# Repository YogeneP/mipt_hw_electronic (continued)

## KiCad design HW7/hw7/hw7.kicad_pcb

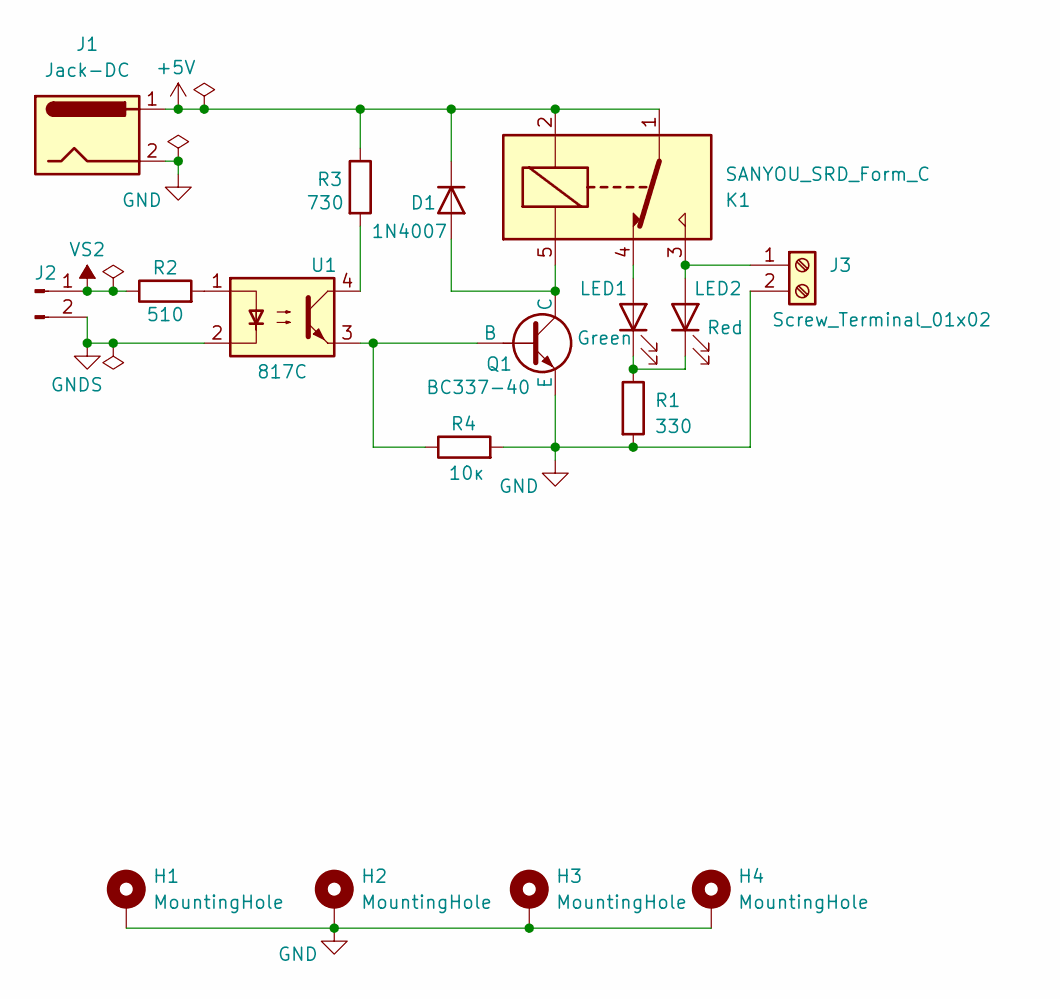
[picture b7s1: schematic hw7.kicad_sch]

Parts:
D1: 1N4007; D_0805_2012Metric
H1, H2, H3, H4: MountingHole; MountingHole_2.2mm_M2_DIN965_Pad
J1: Jack-DC; BarrelJack_GCT_DCJ200-10-A_Horizontal
J2: Conn_01x02_Pin; Molex_KK-254_AE-6410-02A_1x02_P2.54mm_Vertical
J3: Screw_Terminal_01x02; TerminalBlock_Phoenix_MKDS-1,5-2-5.08_1x02_P5.08mm_Horizont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
K1: SANYOU_SRD_Form_C; Relay_SPDT_SANYOU_SRD_Series_Form_C
LED1: Red; LED_1210_3225Metric
LED2: Green; LED_1210_3225Metric
Q1: BC337-40; TO-92L
R1: 330; R_0805_2012Metric_Pad1.20x1.40mm_HandSolder
R2: 510; R_0805_2012Metric_Pad1.20x1.40mm_HandSolder
R3: 730; R_0805_2012Metric_Pad1.20x1.40mm_HandSolder
R4: 10к; R_0805_2012Metric_Pad1.20x1.40mm_HandSolder
U1: 817C; DIP-4_W7.62mm_LongPads

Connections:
+5V: D1.1 (K), J1.1, K1.1, K1.2, R3.1
GND: H1.1, H2.1, H3.1, H4.1, J1.2, J3.2, Q1.3 (E), R1.2, R4.2
GNDS: J2.2, U1.2
unnamed: D1.2 (A), K1.5, Q1.1 (C)
unnamed: J3.1, K1.3, LED2.2 (A)
unnamed: K1.4, LED1.2 (A)
unnamed: LED1.1 (K), LED2.1 (K), R1.1
unnamed: Q1.2 (B), R4.1, U1.3
unnamed: R2.2, U1.1
unnamed: R3.2, U1.4
VS2: J2.1, R2.1

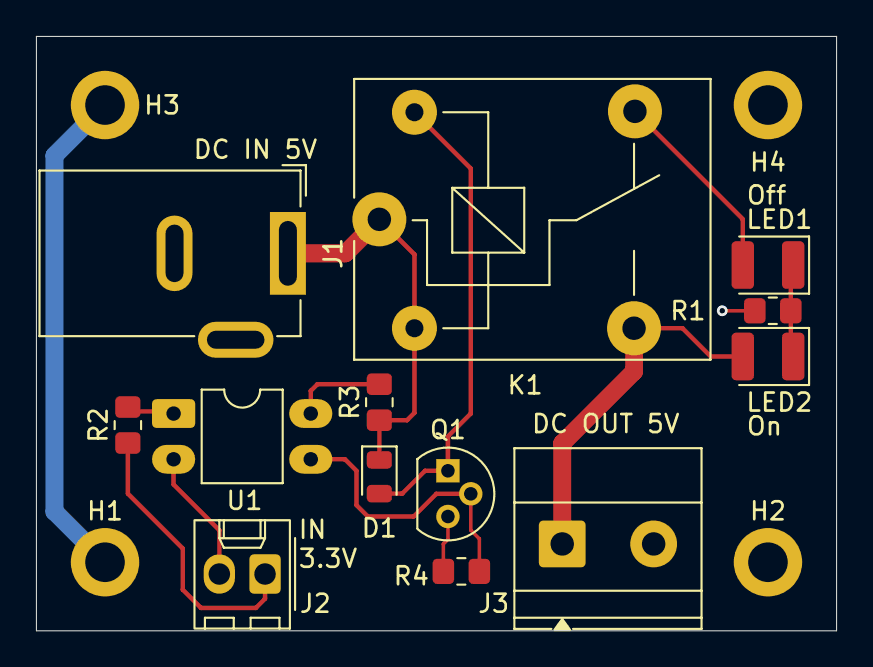
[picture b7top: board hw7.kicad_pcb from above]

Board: 2 copper layers, 44.5 x 33.0 mm, 17 parts (0 on the bottom side), 11 nets.

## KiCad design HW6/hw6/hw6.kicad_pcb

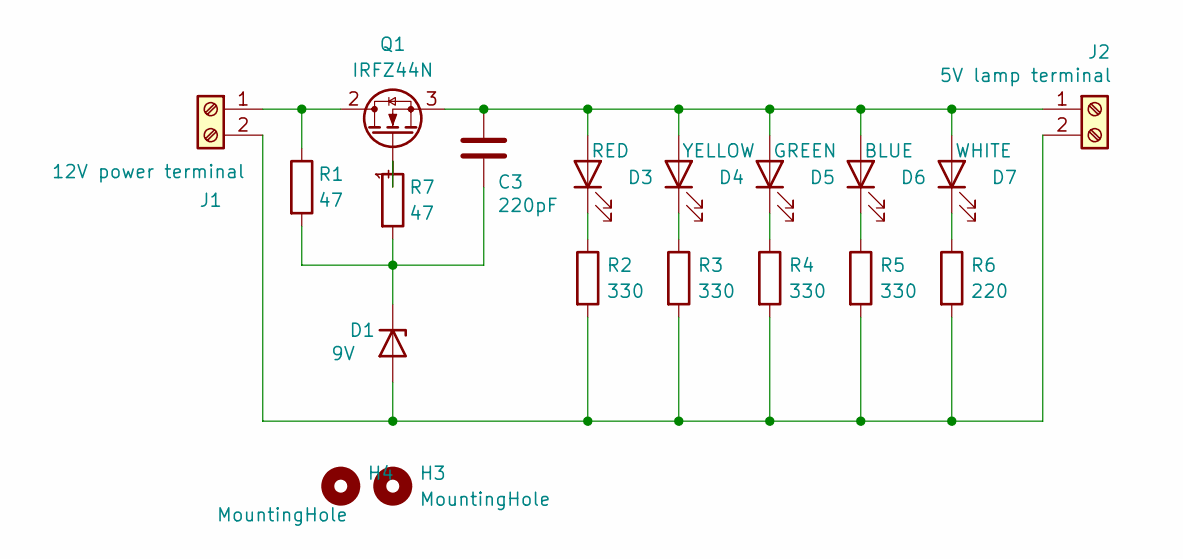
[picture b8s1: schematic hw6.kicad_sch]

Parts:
C3: 220pF; C_0805_2012Metric_Pad1.18x1.45mm_HandSolder
D1: 9V; R_Axial_DIN0207_L6.3mm_D2.5mm_P2.54mm_Vertical
D3: RED; LED_1210_3225Metric
D4: YELLOW; LED_1210_3225Metric
D5: GREEN; LED_1210_3225Metric
D6: BLUE; LED_1210_3225Metric
D7: WHITE; LED_1210_3225Metric
H3, H4: MountingHole; MountingHole_2.2mm_M2_DIN965_Pad
J1: 12V power terminal; TerminalBlock_Phoenix_MKDS-1,5-2-5.08_1x02_P5.08mm_Horizont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
J2: 5V lamp terminal; TerminalBlock_Phoenix_MKDS-1,5-2-5.08_1x02_P5.08mm_Horizont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
Q1: IRFZ44N; TO-220-3_Vertical
R1, R7: 47; R_1206_3216Metric_Pad1.30x1.75mm_HandSolder
R2, R3, R4, R5: 330; R_1206_3216Metric_Pad1.30x1.75mm_HandSolder
R6: 220; R_1206_3216Metric_Pad1.30x1.75mm_HandSolder

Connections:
unnamed: D1.2 (A), H3.1, H4.1, J1.2, J2.2, R2.2, R3.2, R4.2, R5.2, R6.2
unnamed: C3.2, D1.1 (K), R1.2, R7.2
unnamed: C3.1, D3.2 (A), D4.2 (A), D5.2 (A), D6.2 (A), D7.2 (A), J2.1, Q1.3 (S)
unnamed: D3.1 (K), R2.1
unnamed: D4.1 (K), R3.1
unnamed: D5.1 (K), R4.1
unnamed: D6.1 (K), R5.1
unnamed: D7.1 (K), R6.1
unnamed: J1.1, Q1.2 (D), R1.1
unnamed: Q1.1 (G), R7.1

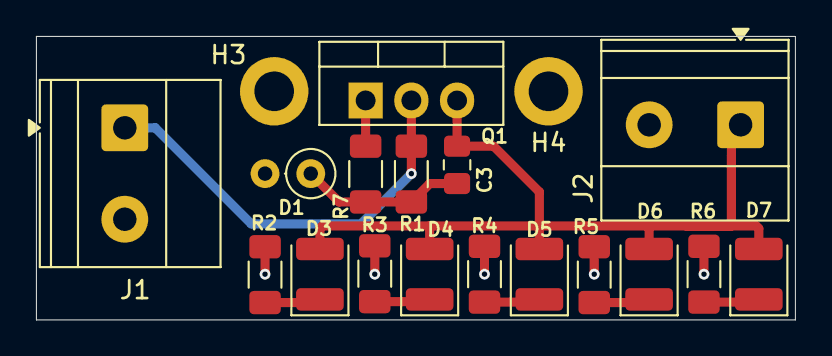
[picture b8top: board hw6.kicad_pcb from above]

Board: 2 copper layers, 42.2 x 15.7 mm, 19 parts (0 on the bottom side), 10 nets.

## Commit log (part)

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2026-03-22 init
2026-03-29 HW4 completed
2026-03-31 HW5 started
2026-04-05 HW4, HW5 complete
2026-04-09 hw6 CircuitJS diagram
2026-04-12 HW6 done. HW7 started
2026-04-13 hw7 proceeding
2026-04-24 HW7-HW8
2026-04-26 HW7 done, HW8 processing
2026-04-27 hw8 processing
2026-05-03 hw9 circuit + PCB + text proceeding
2026-05-04 hw9 done
2026-05-05 hw8 processing, hw9 done
2026-05-09 HW10 processing
2026-05-09 HW8 complete
2026-05-11 HW10 circuit done
2026-05-13 HW10 done
2026-05-17 HW11 circuit begin
2026-05-17 hw11 in progress
2026-05-17 hw11 description proceeding
2026-05-18 hw11 processing
2026-05-21 HW12 PCB done
